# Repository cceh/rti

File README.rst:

RTI
===

The RTI project aims to build an RTI dome.

`Project Documentation <https://cceh.github.io/rti/index.html>`_

Dependencies
------------

Debian

.. code-block:: console

   sudo apt install build-essential liblapacke-dev

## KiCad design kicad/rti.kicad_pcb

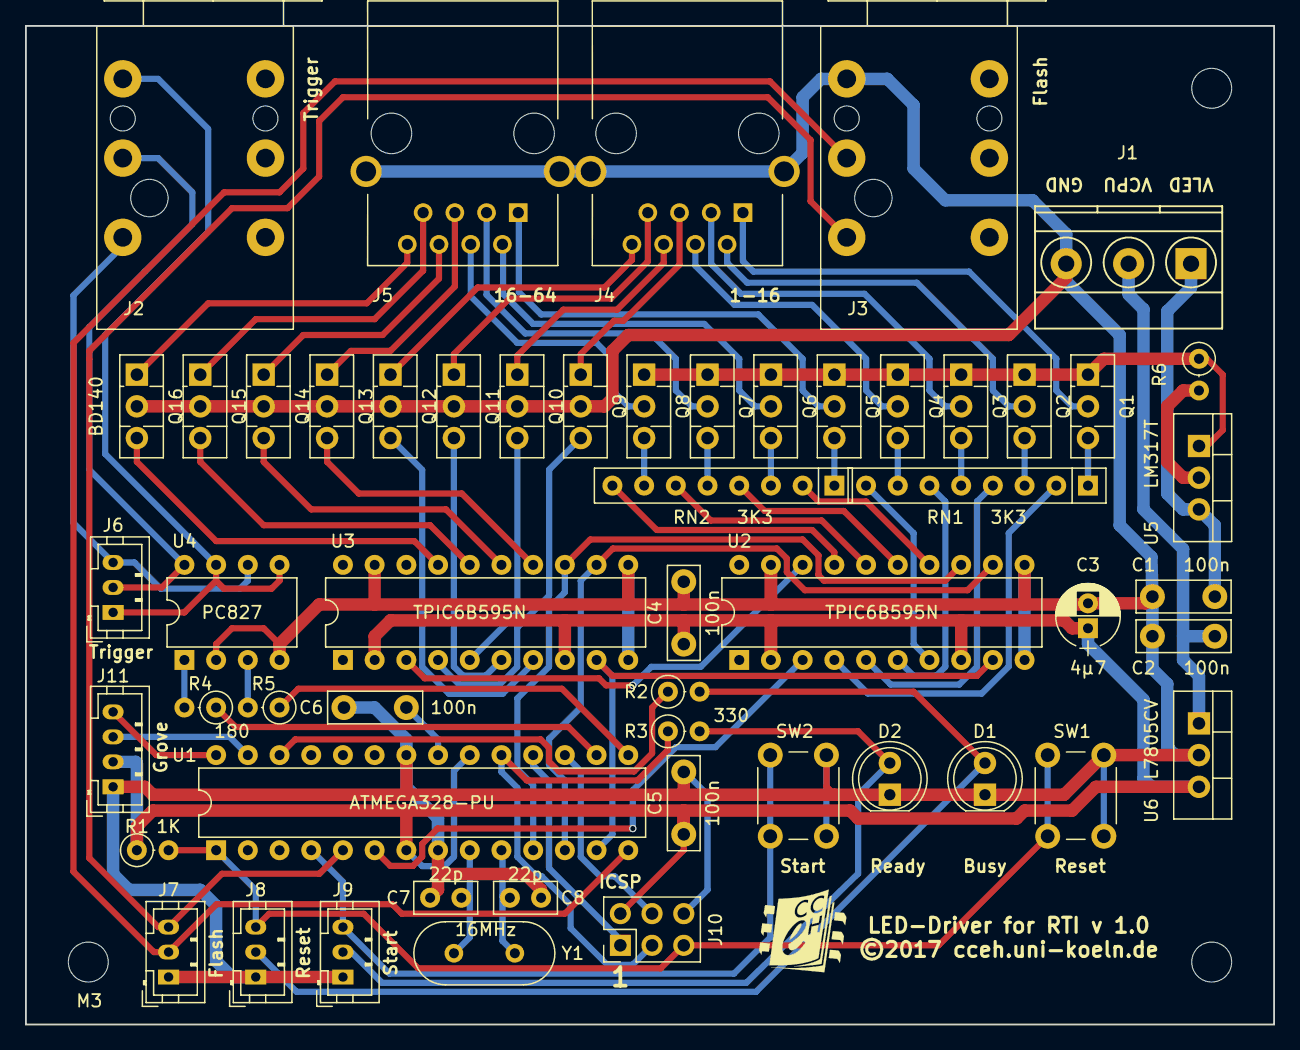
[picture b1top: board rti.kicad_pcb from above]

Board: 2 copper layers, 100.0 x 80.0 mm, 57 parts (0 on the bottom side), 73 nets.

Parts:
C1, C2, C4, C5, C6: 100n; C_Disc_D7.5mm_W2.5mm_P5.00mm
C3: 4µ7; CP_Radial_D5.0mm_P2.00mm
C7, C8: 22p; C_Disc_D5.0mm_W2.5mm_P2.50mm
D1: Red; LED_D5.0mm
D2: Green; LED_D5.0mm
J1: Phoenix MKDS; TerminalBlock_Pheonix_MKDS1.5-3pol
J2, J3: NRJ6HF
J4, J5: MEBP 8-8G; MEBP_8-8G
J6, J7, J8, J9: JST PH 3; JST_PH_B3B-PH-K_03x2.00mm_Straight
J10: Header 2x3; Pin_Header_Straight_2x03_Pitch2.54mm
J11: JST PH 4; JST_PH_B4B-PH-K_04x2.00mm_Straight
M3, M3_2, M3_3: MountingHole_3.2mm_M3_DIN965; MountingHole_3.2mm_M3
Q1, Q2, Q3, Q4, Q5, Q6, Q7, Q8, Q9, Q10, Q11, Q12, Q13, Q14, Q15, Q16: BD140; TO-126_Vertical
R1: 1K; R_Axial_DIN0207_L6.3mm_D2.5mm_P2.54mm_Vertical
R2, R3: 330; R_Axial_DIN0207_L6.3mm_D2.5mm_P2.54mm_Vertical
R4, R5: 180; R_Axial_DIN0207_L6.3mm_D2.5mm_P2.54mm_Vertical
R6: 6R2; R_Axial_DIN0207_L6.3mm_D2.5mm_P2.54mm_Vertical
RN1, RN2: 3K3; R_Array_SIP8
SW1, SW2: Switch; SW_PUSH_6mm_h7.3mm
U1: ATMEGA328-PU; DIP-28_W7.62mm
U2, U3: TPIC6B595N; DIP-20_W7.62mm
U4: PC827; DIP-8_W7.62mm
U5: LM317T; TO-220_Vertical
U6: L7805CV; TO-220_Vertical
Y1: 16MHz; Crystal_HC49-U_Vertical

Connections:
+5V: C3.1, C4.1, C5.1, J10.2, J11.2, R1.1, U1.7, U1.20, U2.2, U2.8, U3.2, U3.8, U6.3
/+200mA: Q1.1, Q2.1, Q3.1, Q4.1, Q5.1, Q6.1, Q7.1, Q8.1, R6.1, U5.1
/A3: R2.1, U1.26
/An0: J4.1, Q1.2
/An1: J4.2, Q2.2
/An2: J4.3, Q3.2
/An3: J4.4, Q4.2
/An4: J5.1, Q5.2
/An5: J5.2, Q6.2
/An6: J5.3, Q7.2
/An7: J5.4, Q8.2
/Cat0: J4.5, Q9.1
/Cat1: J4.6, Q10.1
/Cat2: J4.7, Q11.1
/Cat3: J4.8, Q12.1
/Cat4: J5.5, Q13.1
/Cat5: J5.6, Q14.1
/Cat6: J5.7, Q15.1
/Cat7: J5.8, Q16.1
/D2: J9.3, SW2.2, U1.4
/D3: J3.1, J7.3, U1.5
/D4: U1.6, U2.3
/D5: U1.11, U2.13, U3.13
/D6: U1.12, U2.12, U3.12
/D7: U1.13, U2.9, U3.9
/D8: J3.2, J7.2, U1.14
/D9: R5.1, U1.15
/D10: R4.1, U1.16
/D11: J10.4, U1.17
/D12: J10.1, U1.18
/D13: J10.3, R3.1, U1.19
/HC1: R6.2, U5.2
/SCL: J11.4, U1.28
/SDA: J11.3, U1.27
/VINCPU: C2.1, J1.2, U6.1
/VINLED: C1.1, J1.1, U5.3
/~RESET: J8.3, J10.5, R1.2, SW1.2, U1.1
GND: C1.2, C2.2, C3.2, C4.2, C5.2, C6.2, C7.1, C8.1, D1.1, D2.1, J1.3, J3.3, J4.9, J5.9, J7.1, J8.1, J9.1, J10.6, J11.1, Q9.2, Q10.2, Q11.2, Q12.2, Q13.2, Q14.2, Q15.2, Q16.2, SW1.1, SW2.1, U1.8, U1.22, U2.10, U2.11, U2.19, U3.10, U3.11, U3.19, U4.2, U4.4, U6.2
unnamed: C6.1, U1.21
unnamed: C7.2, U1.9, Y1.1
unnamed: C8.2, U1.10, Y1.2
unnamed: D1.2, J8.2, R2.2
unnamed: D2.2, J9.2, R3.2
unnamed: J2.1, J6.3, U4.6
unnamed: J2.2, J6.2, U4.8
unnamed: J2.3, J6.1, U4.5, U4.7
unnamed: Q1.3, RN1.1
unnamed: Q2.3, RN1.3
unnamed: Q3.3, RN1.5
unnamed: Q4.3, RN1.7
unnamed: Q5.3, RN2.1
unnamed: Q6.3, RN2.3
unnamed: Q7.3, RN2.5
unnamed: Q8.3, RN2.7
unnamed: Q9.3, U3.4
unnamed: Q10.3, U3.5
unnamed: Q11.3, U3.6
unnamed: Q12.3, U3.7
unnamed: Q13.3, U3.14
unnamed: Q14.3, U3.15
unnamed: Q15.3, U3.16
unnamed: Q16.3, U3.17
unnamed: R4.2, U4.1
unnamed: R5.2, U4.3
unnamed: RN1.2, U2.4
unnamed: RN1.4, U2.5
unnamed: RN1.6, U2.6
unnamed: RN1.8, U2.7
unnamed: RN2.2, U2.14
unnamed: RN2.4, U2.15
unnamed: RN2.6, U2.16
unnamed: RN2.8, U2.17
unnamed: U2.18, U3.3

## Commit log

2017-05-29 WIP. Add Kicad schematic.
2017-06-06 WIP Add PCB.
2017-06-06 WIP. Add pretty picture.
2017-06-12 Get rid of Arduino overhead.
    Change program to use ATmega port names instead of Arduino.
    Add ISP programming in Makefile.
    Renumber and move transistors.
2017-06-21 Get rid of Arduino physically. Add case. New board layout.
2017-06-26 Add BOM.
2017-07-04 WIP. Use ceramic C and R arrays.
2017-07-05 Change LED connectors pinout
    Implements a less spectacular failure mode if LED connectors
    are switched, ie. flashes them in the wrong order instead of
    burning them all.
2017-07-06 Update picture.
2017-07-23 Separate cmd to init fuses.
2017-07-23 Add jack for external start switch.
2017-07-23 Prototype now has 16 LEDs.
2017-07-23 Add some images of the first completed prototype.
2017-11-16 Add docs about RTI. Make docs into github pages.
2017-11-16 Fix nojekyll.
2017-11-21 Documentation improvements.
2017-11-24 Add proof of concept PTM decoder.
2017-12-18 Implement the encoder. Refactor code into library.
2017-12-28 WIP on docs.
2018-01-22 WIP.
2018-01-25 WIP docs.
2018-11-13 Fix width bug with rectangular pictures.
2018-11-13 Implement long / short button press.
2018-11-13 Quick and dirty fix for debounce.
2018-11-26 WIP on docs and LRGB format.
2018-11-28 WIP on PTM formats and docs.
2018-12-04 RTIViewer compatibility.
2018-12-04 More preprocessing power to the scripts.
2019-05-24 Fixing Makefile to create BUILDDIR and BINDIR.
2019-05-24 Build dependencies
2019-07-11 Update docs.
2019-07-12 Improve docs.
2020-01-14 fix image filer
2020-01-14 update docs
2020-01-14 fix Makefile targets
2020-01-15 Fix MacOS segfault on scanf.
    scanf %ms is in POSIX since 2008, but somehow Apple never found
    the time to implement it.
2020-01-15 Update docs. Update Sphinx.
2020-01-28 More docs.
2023-04-14 program first led on power on
2023-08-01 Fixes #3 multiple definition of ptm_formats in gcc 10+
2023-08-01 Fix lots of Sonar complaints
2023-08-01 Add test and clean targets
2023-08-01 Update kicad format

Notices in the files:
kicad/rti.kicad_pcb:
©2017 cceh.uni-koeln.de
